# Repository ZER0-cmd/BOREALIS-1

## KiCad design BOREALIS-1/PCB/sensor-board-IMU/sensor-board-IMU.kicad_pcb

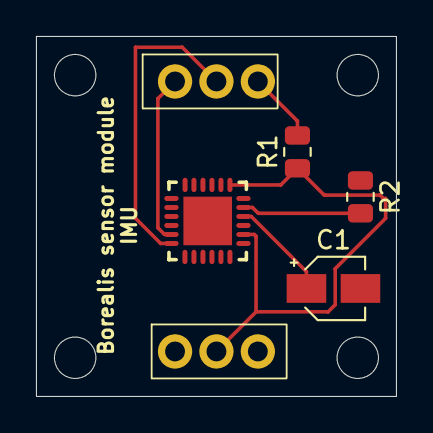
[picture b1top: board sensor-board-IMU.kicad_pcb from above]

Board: 2 copper layers, 20.0 x 20.0 mm, 6 parts (0 on the bottom side), 7 nets.

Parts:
C1: 0.1 microf; CP_Elec_3x5.3
J2: Conn_01x03_Pin (data connection to main board); 1x03 2.3 pitch
J5: Conn_01x03_Pin (power connection to main board); 1x03 2.3 pitch
MPU6050: MPU6050-footprint
R1: R; R_0805_2012Metric
R2: 10k; R_0805_2012Metric

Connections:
+3.3V: J5.2, MPU6050.8 (VLOGIC), MPU6050.13 (VDD), R1.1
/ADC: J2.3, R1.2
/SCL: J2.1, MPU6050.23 (SCL)
/SDA: J2.2, MPU6050.24 (SDA)
GND: C1.2, J5.1, MPU6050.18 (GND), R2.1
unnamed: MPU6050.9 (AD0), MPU6050.11 (FSYNC), R2.2
unnamed: C1.1, MPU6050.10 (REGOUT)

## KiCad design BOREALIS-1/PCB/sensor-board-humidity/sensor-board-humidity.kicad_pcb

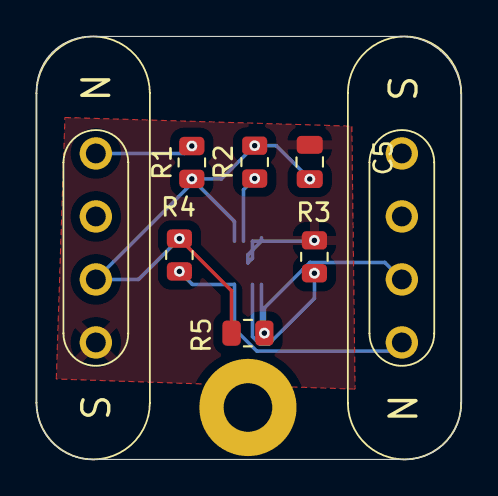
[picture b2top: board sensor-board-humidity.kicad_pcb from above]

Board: 2 copper layers, 23.6 x 23.5 mm, 10 parts (1 on the bottom side), 7 nets.

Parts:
C5: 100nf; C_0805_2012Metric
H1: MountingHole; MountingHole_2.7mm_M2.5_Pad
R1: R; R_0805_2012Metric
R2, R3, R4, R5: 10k; R_0805_2012Metric
SHT31: sht31-footprint
U1, U2: MAGNETIC POGO CONN.

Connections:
+3.3V: C5.1, R1.1, R2.2, R4.1, R5.2, SHT31.5 (VDD), U2.2
/ID: R1.2, U2.4
/SCL: R4.2, SHT31.4 (SCL), U1.4
/SDA: R5.1, SHT31.1 (SDA), U1.3
GND: C5.2, R3.1, SHT31.7 (R), SHT31.8 (VSS), SHT31.9 (EP), U2.1
unnamed: R3.2, SHT31.2 (ADDR)
unnamed: R2.1, SHT31.6 (nRESET)

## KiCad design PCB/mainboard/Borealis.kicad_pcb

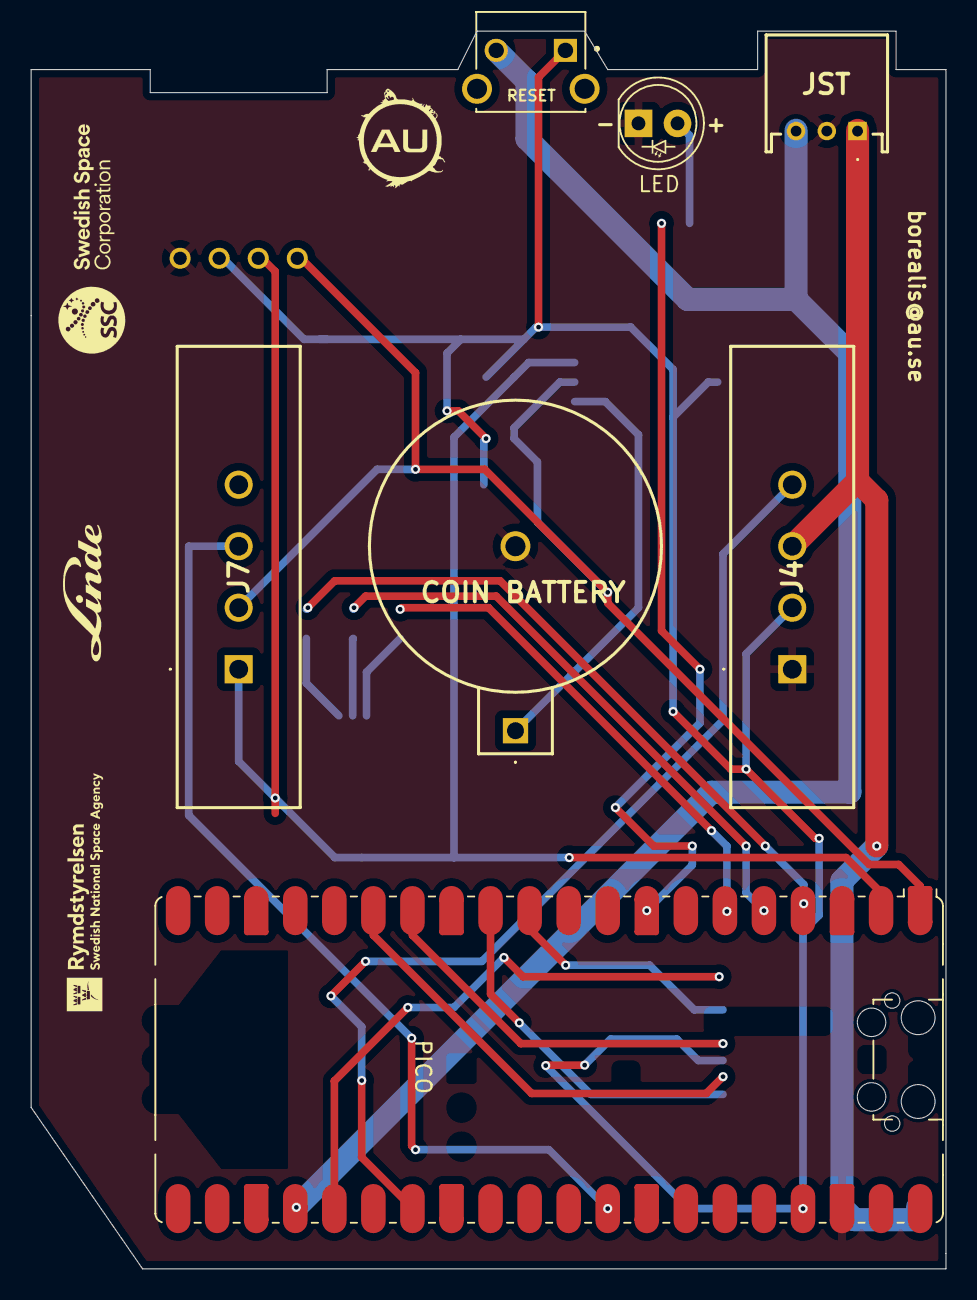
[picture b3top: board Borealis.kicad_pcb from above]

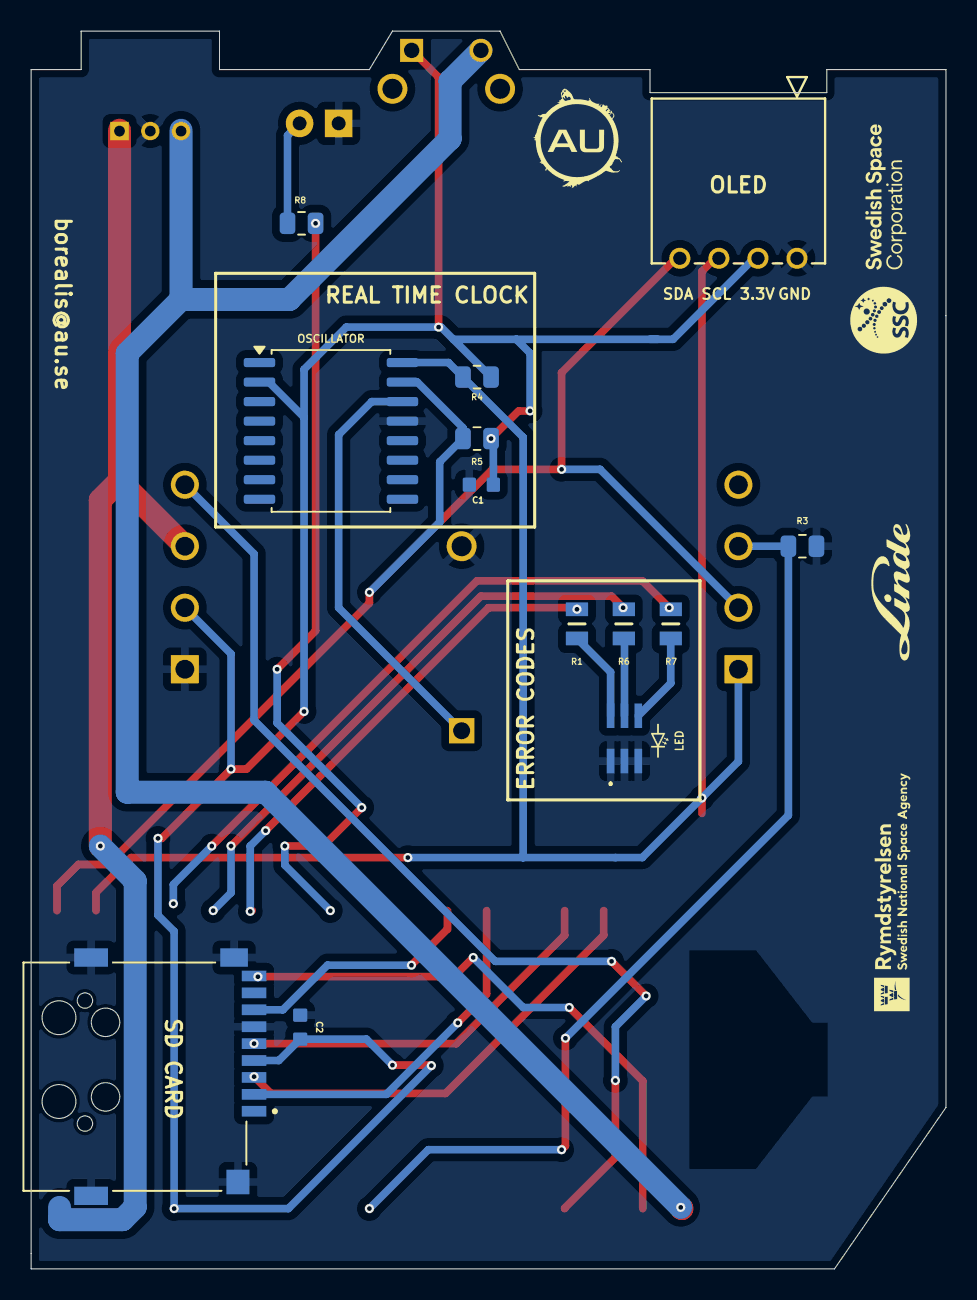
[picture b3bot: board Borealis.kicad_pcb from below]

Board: 2 copper layers, 59.5 x 80.5 mm, 20 parts (13 on the bottom side), 22 nets.

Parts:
C1: 1uF; CAPC1608X90N
C2: 4.7uF; CAPC1608X90N
COIN BATTERY: BAT-HLD-011-THM; BATHLD011THM
D2: LED; LED_D5.0mm
J4, J7: 878-22-004-10-011101; 8782200410011101
JST: S3B-PH-K-S-GW; S3BPHKSGW
LED: ASMT-YTD2-0BB02; ASMTYTD20BB02
OLED: PPTC041LGBN-RC; CONN_PPTC041LGBN-RC_SUL
OSCILLATOR: DS3231SN#T&R; SOIC-16W_7.5x10.3mm_P1.27mm
PICO: Pico; RaspberryPi_Pico_Common_SMD
R1, R6, R7: MCU08050C3300FP500; RESC2012X55N
R3, R8: R; R_0805_2012Metric
R4, R5: 10K; R_0805_2012Metric
SD CARD: MSD-1-A; CUI_MSD-1-A
SW2: TL1105SF160Q; SW_TL1105SF160Q

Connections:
+3.3V: C1.2, C2.2, J4.2, OLED.2, OSCILLATOR.2 (VCC), PICO.37 (3V3_EN), R4.1, R5.1, SD CARD.4 (3.3V), SW2.1
+5V: J4.3, JST.1, PICO.40 (VBUS)
/ADC: J7.3, PICO.32 (GPIO27_ADC1), R3.1
/BLUE: PICO.6 (GPIO4), R1.2
/Detect: PICO.25 (GPIO19), SD CARD.CD (Detetect/Sense)
/GREEN: PICO.5 (GPIO3), R6.2
/ID: J4.4, PICO.27 (GPIO21)
/LED: PICO.8 (GND), R8.1
/RED: PICO.4 (GPIO2), R7.2
/SCL: J7.1, OLED.3, OSCILLATOR.16 (SCL), PICO.2 (GPIO1), R4.2
/SDA: J7.2, OLED.4, OSCILLATOR.15 (SDA), PICO.1 (GPIO0), R5.2
/SPI1 CSn: PICO.12 (GPIO9), SD CARD.2 (CS)
/SPI1 RX: PICO.11 (GPIO8), SD CARD.7 (DO)
/SPI1 SCK: PICO.14 (GPIO10), SD CARD.5 (SCLK)
/SPI1 TX: PICO.15 (GPIO11), SD CARD.3 (DI)
/VBAT: COIN BATTERY.1, OSCILLATOR.14 (VBAT)
/reset: JST.3, PICO.24 (GPIO18), SW2.2
GND: C1.1, C2.1, COIN BATTERY.2, D2.1 (K), J4.1, JST.2, LED.1 (K(BLUE)), LED.2 (K(GREEN)), LED.3 (K(RED)), OLED.1, OSCILLATOR.13 (GND), PICO.38 (GND), R3.2, SD CARD.6 (GND), SD CARD.G1 (COVER_GND), SD CARD.G2 (COVER_GND__1), SD CARD.G3 (COVER_GND__2), SD CARD.G4 (COVER_GND__3)
unnamed: D2.2 (A), R8.2
unnamed: LED.6 (A(BLUE)), R1.1
unnamed: LED.5 (A(GREEN)), R6.1
unnamed: LED.4 (A(RED)), R7.1

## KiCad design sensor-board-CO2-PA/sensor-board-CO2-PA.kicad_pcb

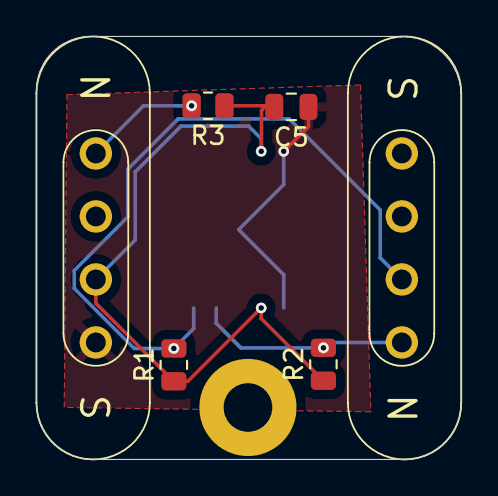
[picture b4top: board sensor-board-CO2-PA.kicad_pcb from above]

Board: 2 copper layers, 23.6 x 23.5 mm, 8 parts (1 on the bottom side), 5 nets.

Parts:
C5: 10microf; C_0805_2012Metric
H1: MountingHole; MountingHole_2.7mm_M2.5_Pad
R1: 10K; R_0805_2012Metric
R2: 10k; R_0805_2012Metric
R3: R; R_0805_2012Metric
U1, U2: MAGNETIC POGO CONN.
U1#2: SCD40-D-R2; SCD40 footprint

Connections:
+3.3V: C5.2, R1.1, R2.1, R3.1, U1#2.7 (VDD), U1#2.19 (VDDH), U2.2
/ID: R3.2, U2.4
/SCL: R2.2, U1.4, U1#2.9 (SCL)
/SDA: R1.2, U1.3, U1#2.10 (SDA)
GND: C5.1, U1#2.6 (GND), U1#2.20 (GND), U1#2.21 (GND), U2.1

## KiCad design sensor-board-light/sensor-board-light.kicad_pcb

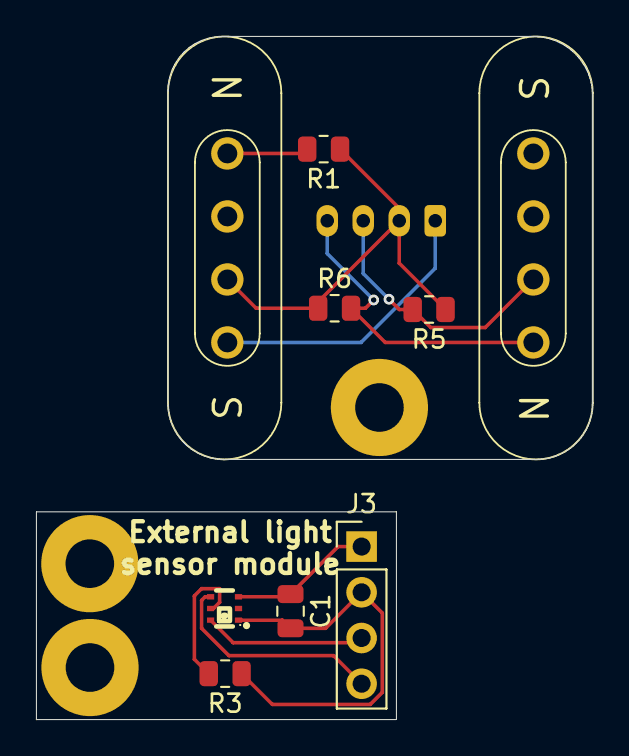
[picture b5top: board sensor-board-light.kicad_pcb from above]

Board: 2 copper layers, 30.9 x 38.0 mm, 13 parts (1 on the bottom side), 9 nets.

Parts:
C1: 100nF; C_0805_2012Metric
H1, H2, H3: MountingHole; MountingHole_2.7mm_M2.5_Pad
J1: Conn_01x04_Pin; JST_PH_B4B-PH-K_1x04_P2.00mm_Vertical
J3: Conn_01x04_Pin; PinHeader_1x04_P2.54mm_Vertical
LTR-390UV-01: SENSOR-SMD_LTR-390UV-01
R1: R; R_0805_2012Metric
R3, R5, R6: 10k; R_0805_2012Metric
U1, U2: MAGNETIC POGO CONN.

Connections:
+3.3V: J1.2, R1.1, R5.1, R6.1, U2.2
/3.3v: C1.2, J3.2, LTR-390UV-01.1 (VDD), R3.1
/ID: R1.2, U2.4
/SCL: J1.4, R6.2, U1.4
/SCL1: J3.4, LTR-390UV-01.4 (SCL)
/SDA: J1.3, R5.2, U1.3
/SDA1: J3.3, LTR-390UV-01.6 (SDA)
GND: C1.1, J1.1, J3.1, LTR-390UV-01.3 (GND), U2.1
unnamed: LTR-390UV-01.5 (INT), R3.2

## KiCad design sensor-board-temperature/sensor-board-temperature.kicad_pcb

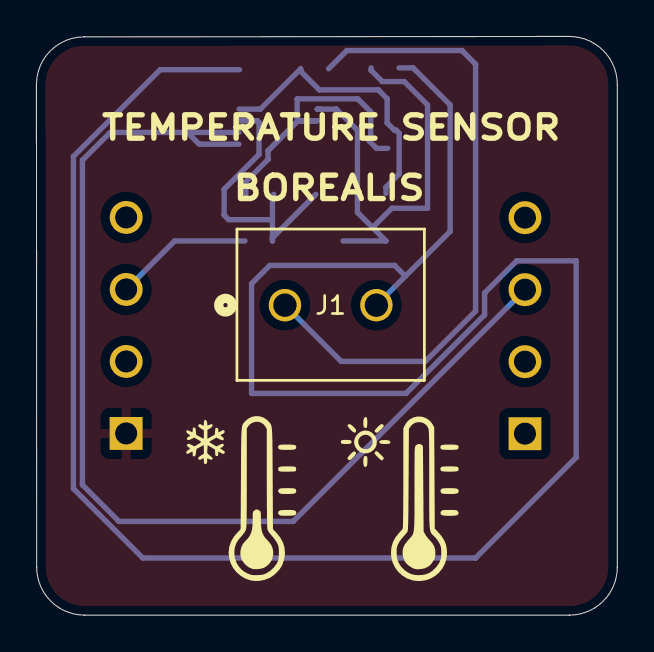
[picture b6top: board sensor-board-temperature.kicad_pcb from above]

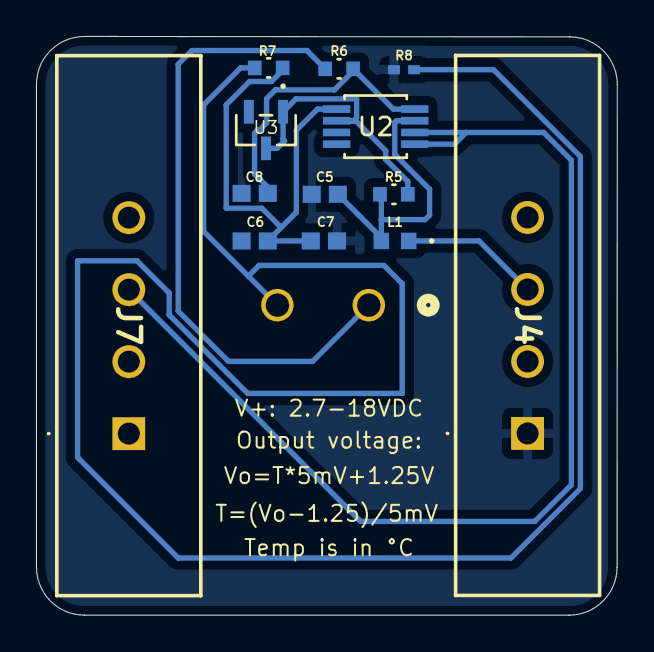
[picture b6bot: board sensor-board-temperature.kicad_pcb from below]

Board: 2 copper layers, 32.3 x 32.2 mm, 14 parts (13 on the bottom side), 9 nets.

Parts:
C5, C6, C7, C8: C0603C104K5RACTU; CAPC17595_95N_KEM
J1: 1729128; CONN_1729128_PXC
J4, J7: 878-22-004-10-011101; 8782200410011101
L1: ILHB0603ER121V; IND_VISHAY_ILHB0603_VIS
R5, R6, R7: RC0603FR-07100RL; RC0603N_YAG
R8: RC0402FR-071ML; RC0402N_YAG
U2: AD8495ARMZ; RM_8_ADI
U3: TLVH431BIL3T; SOT23-3-L_3p04x1p4x1p9_STM

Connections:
+5V: J4.3, L1.1
/ADC: J7.3, U2.5 (SENSE), U2.6 (OUT)
GND: C5.2, C7.2, C8.2, J4.1, R8.2, U2.3 (VS-), U3.2 (CATHODE)
unnamed: J1.1, R6.2
unnamed: J1.2, R7.2, R8.1
unnamed: C6.2, C8.1, R6.1, U2.8 (+IN)
unnamed: C6.1, C7.1, R7.1, U2.1 (IN-)
unnamed: R5.1, U2.2 (REF), U3.1 (REF), U3.3 (ANODE)
VCC: C5.1, L1.2, R5.2, U2.7 (+VS)
